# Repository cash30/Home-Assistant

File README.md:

# Home-Assistant

A home assistant, similar to alexa but local!

## Screenshots

Here's the workflow:

<p>
ESP32<br>
⬇️<br>
Server<br>
⬇️<br>
OpenWakeWord (wakeword)<br>
⬇️<br>
Faster-whisper (STT)<br>
⬇️<br>
My desktop (for the GPU)<br>
⬇️<br>
Ollama<br>
⬇️<br>
Back to server<br>
⬇️<br>
Piper (TTS)<br>
⬇️<br>
Back to ESP32<br>
  <br><br><br>
</p>

Here's a list of parts:<br>
1x ESP32-S3 ReSpeaker-lite - 30.99 https://www.seeedstudio.com/ReSpeaker-Lite-Voice-Assistant-Kit-p-5929.html<br>
1x USBC Charger - 12.99 https://www.seeedstudio.com/27W-USB-C-PD-Power-Supply-Black-US-Version-p-5812.html<br>
1x 3D printed shell<br><br>
Total: 43.98<br>

Here's the link to the CAD:  
https://cad.onshape.com/documents/3b531fa6d3b48e1133fff80f/w/1dff5b39a6036095855b317d/e/03ff1a39b6a9a2e8eaf5ee01

I hope that ive put enough here.. idk what else to write.

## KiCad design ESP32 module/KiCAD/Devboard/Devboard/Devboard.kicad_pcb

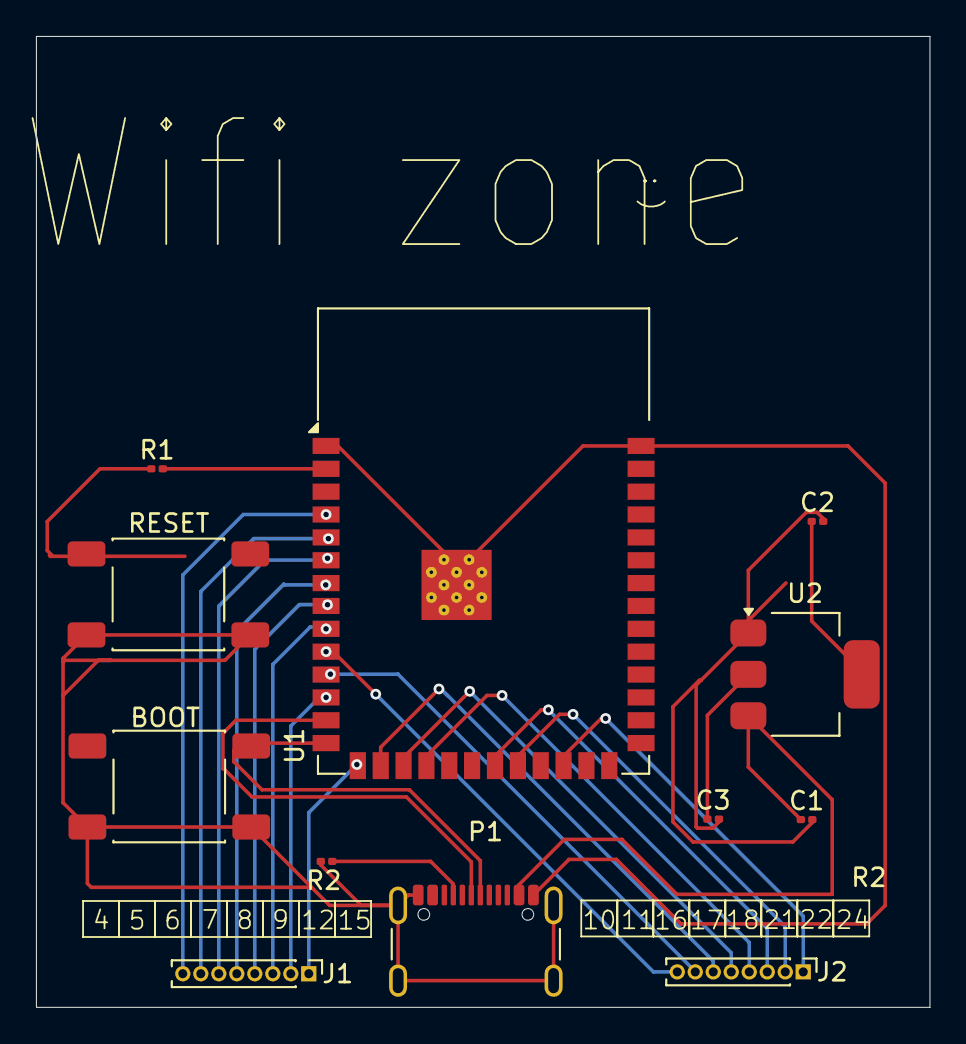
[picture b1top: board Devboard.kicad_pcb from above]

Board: 2 copper layers, 49.6 x 53.9 mm, 12 parts (0 on the bottom side), 25 nets.

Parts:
BOOT: SW_Push; SW_Push_1P1T_NO_E-Switch_TL3301NxxxxxG
C1: 10uF; C_0201_0603Metric
C2: C_Polarized; C_0201_0603Metric
C3: 0.1uF; C_0201_0603Metric
J1, J2: Conn_01x08_Pin; PinHeader_1x08_P1.00mm_Vertical
P1: USB_C_Plug_USB2.0; USB_C_Receptacle_GCT_USB4105-xx-A_16P_TopMnt_Horizontal
R1, R2: 5.1k; R_0201_0603Metric
RESET: SW_Push; SW_Push_1P1T_NO_E-Switch_TL3301NxxxxxG
U1: ESP32-S3-WROOM-1
U2: AMS1117-3.3; SOT-223-3_TabPin2

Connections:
GND: BOOT.2, C1.2, C2.2, R2.2, RESET.2, U1.1 (GND), U1.40 (GND), U1.41 (GND)
unnamed: J1.1, U1.15 (IO3)
unnamed: J1.2, U1.12 (IO8)
unnamed: J1.3, U1.9 (IO16)
unnamed: J1.4, U1.8 (IO15)
unnamed: J1.5, U1.7 (IO7)
unnamed: J1.6, U1.6 (IO6)
unnamed: J1.7, U1.5 (IO5)
unnamed: J1.8, U1.4 (IO4)
unnamed: J2.1, U1.24 (IO47)
unnamed: J2.2, U1.22 (IO14)
unnamed: J2.3, U1.21 (IO13)
unnamed: J2.4, U1.18 (IO10)
unnamed: J2.5, U1.17 (IO9)
unnamed: J2.6, U1.16 (IO46)
unnamed: J2.7, U1.11 (IO18)
unnamed: J2.8, U1.10 (IO17)
unnamed: P1.A5 (CC), R2.1
unnamed: P1.A6 (D+), U1.13 (USB_D-)
unnamed: P1.A7 (D-), U1.14 (USB_D+)
unnamed: C3.2, P1.A1 (GND), P1.A12 (GND), P1.B1 (GND), P1.B12 (GND), P1.S1 (SHIELD), U2.1 (GND)
unnamed: C2.1, C3.1, R1.2, U1.2 (3V3), U2.2 (VO)
unnamed: R1.1, RESET.1, U1.3 (EN)
unnamed: BOOT.1, U1.27 (IO0)
unnamed: C1.1, P1.A4 (VBUS), P1.A9 (VBUS), P1.B4 (VBUS), P1.B9 (VBUS), U2.3 (VI)
